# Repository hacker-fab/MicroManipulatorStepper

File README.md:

# HackerFab Nanopositioner

This repository contains **HackerFab’s extended version** of the open-source nanopositioner originally developed by Diffraction Limited.

We build directly on the original design and contribute additional capabilities, including:
- Rotational control
- Integrated heating
- Vacuum compatibility
- Ongoing improvements for lab use at HackerFab

## Credit

All core mechanical, electrical, and firmware design work is credited to the original project:

https://github.com/0x23/OpenMicroManipulator  

This repo is a derivative work that extends their platform for new use cases with additional custom made components. 

## Documentation

For build instructions, usage, and full system details, see the HackerFab documentation:

https://docs.hackerfab.org/home

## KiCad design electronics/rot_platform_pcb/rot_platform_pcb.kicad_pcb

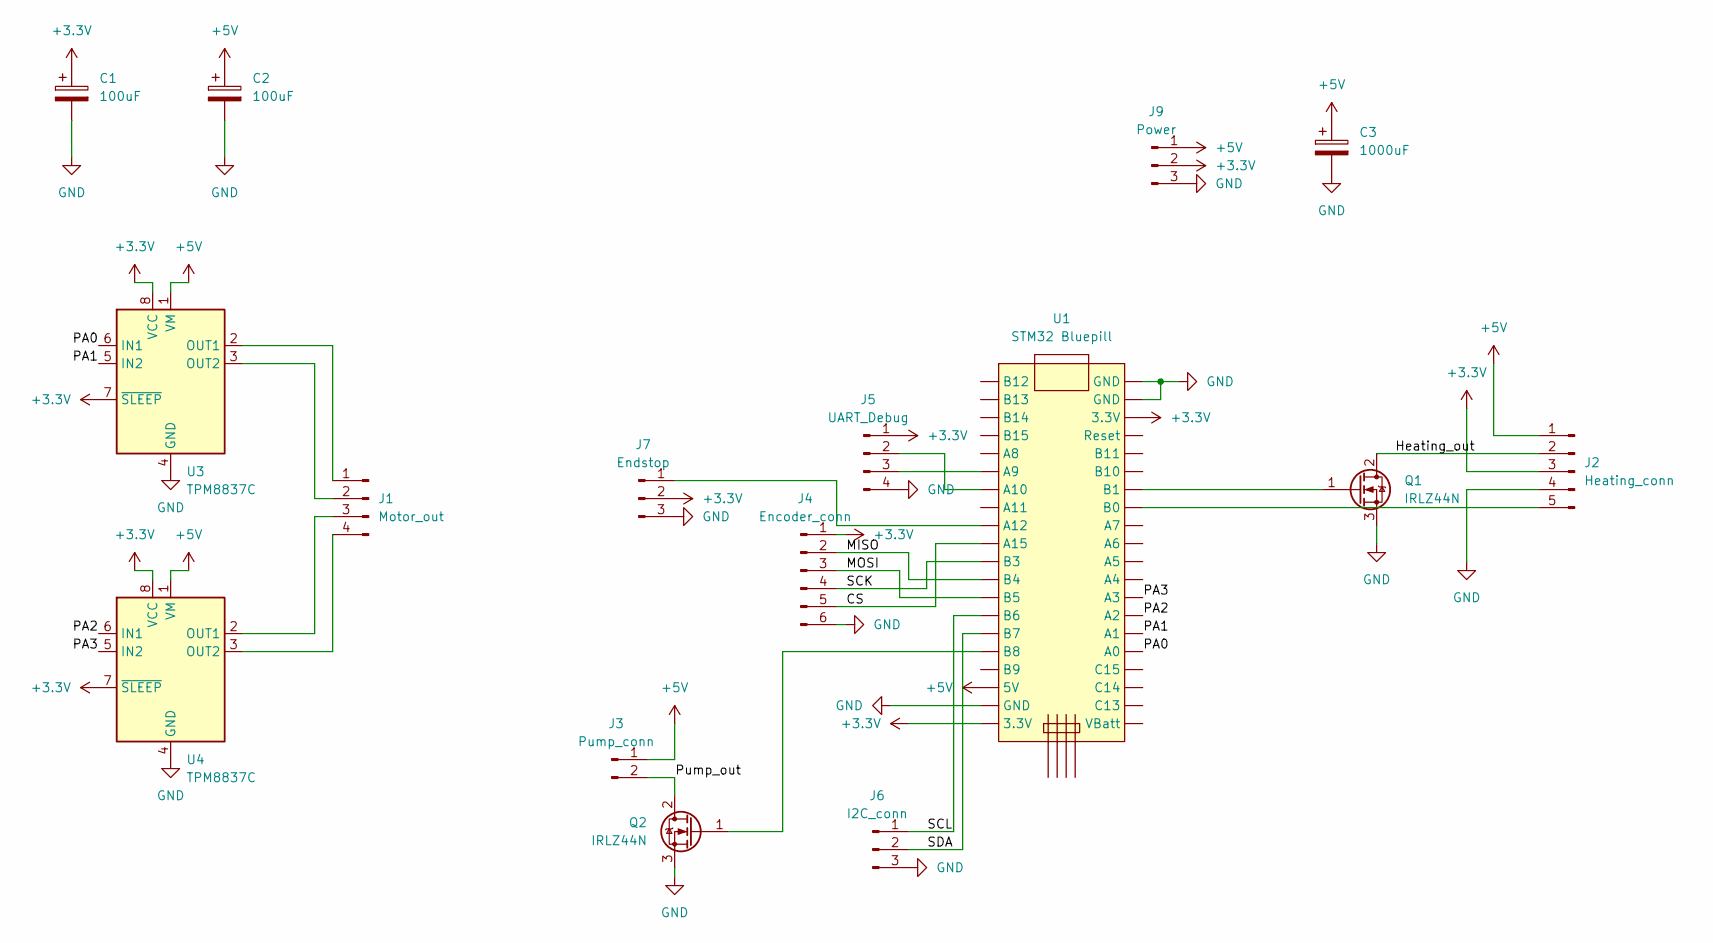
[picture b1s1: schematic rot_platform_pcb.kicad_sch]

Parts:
C1, C2: 100uF; CP_Radial_D5.0mm_P2.50mm
C3: 1000uF; CP_Radial_D10.0mm_P5.00mm
J1: Motor_out; PinHeader_1x04_P2.54mm_Vertical
J2: Heating_conn; PinHeader_1x05_P2.54mm_Vertical
J3: Pump_conn; PinHeader_1x02_P2.54mm_Vertical
J4: Encoder_conn; PinHeader_1x06_P2.54mm_Vertical
J5: UART_Debug; PinHeader_1x04_P2.54mm_Vertical
J6: I2C_conn; PinHeader_1x03_P2.54mm_Vertical
J7: Endstop; PinHeader_1x03_P2.54mm_Vertical
J9: Power; PinHeader_1x03_P2.54mm_Vertical
Q1, Q2: IRLZ44N; TO-220-3_Vertical
U1: STM32 Bluepill; stm32_bluepill
U3, U4: TPM8837C; SOIC-8-1EP_3.9x4.9mm_P1.27mm_EP2.29x3mm

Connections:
+3.3V: C1.1, J2.3, J4.1, J5.1, J7.2, J9.2, U1.20 (3.3V), U1.38 (3.3V), U3.7 (~SLEEP), U3.8 (VCC), U4.7 (~SLEEP), U4.8 (VCC)
+5V: C2.1, C3.1, J2.1, J3.1, J9.1, U1.18 (5V), U3.1 (VM), U4.1 (VM)
/CS: J4.5, U1.10 (A15)
/Heating_out: J2.2, Q1.2 (D)
/MISO: J4.2, U1.12 (B4)
/MOSI: J4.3, U1.13 (B5)
/PA0: U1.25 (A0), U3.6 (IN1)
/PA1: U1.26 (A1), U3.5 (IN2)
/PA2: U1.27 (A2), U4.6 (IN1)
/PA3: U1.28 (A3), U4.5 (IN2)
/Pump_out: J3.2, Q2.2 (D)
/SCK: J4.4, U1.11 (B3)
/SCL: J6.1, U1.14 (B6)
/SDA: J6.2, U1.15 (B7)
/Temp_in: J2.5, U1.33 (B0); also elsewhere on the board
GND: C1.2, C2.2, C3.2, J2.4, J4.6, J5.4, J6.3, J7.3, J9.3, Q1.3 (S), Q2.3 (S), U1.19 (GND), U1.39 (GND), U1.40 (GND), U3.4 (GND), U3.9 (GND), U4.4 (GND), U4.9 (GND); also elsewhere on the board
unnamed: J1.1, U3.2 (OUT1)
unnamed: J1.2, U3.3 (OUT2)
unnamed: J1.3, U4.2 (OUT1)
unnamed: J1.4, U4.3 (OUT2)
unnamed: J5.2, U1.7 (A10)
unnamed: J5.3, U1.6 (A9)
unnamed: J7.1, U1.9 (A12)
unnamed: Q1.1 (G), U1.34 (B1)
unnamed: Q2.1 (G), U1.16 (B8)

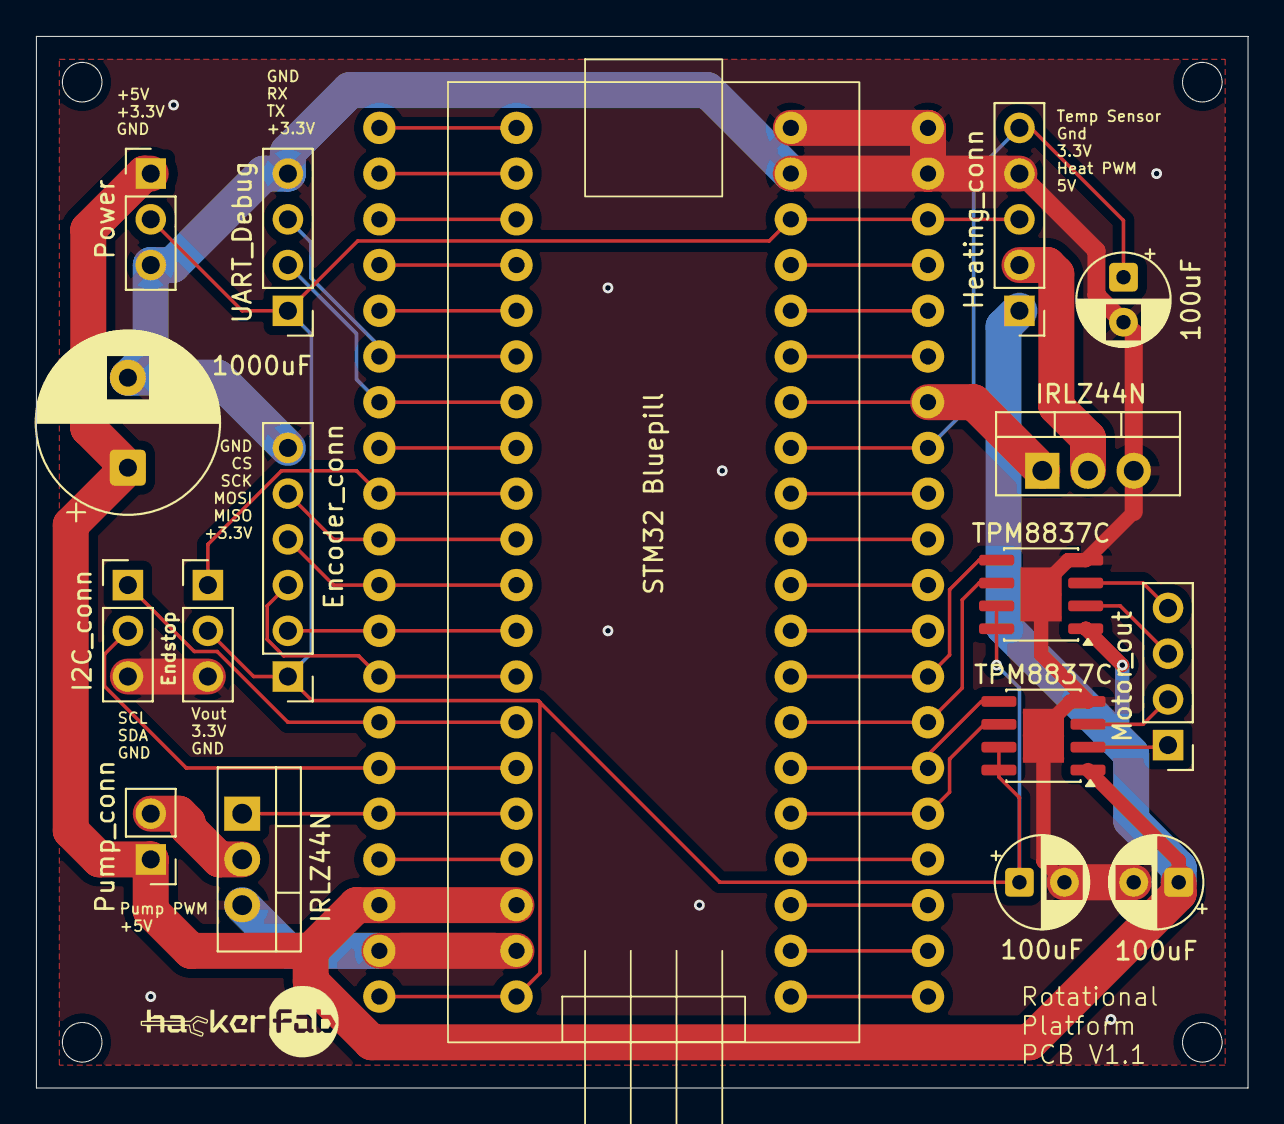
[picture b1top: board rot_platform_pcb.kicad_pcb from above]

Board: 2 copper layers, 67.3 x 58.4 mm, 17 parts (0 on the bottom side), 25 nets.

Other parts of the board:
C4: 100uF; CP_Radial_D5.0mm_P2.50mm

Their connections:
/Temp_in: C4.1; also elsewhere on the board
GND: C4.2; also elsewhere on the board

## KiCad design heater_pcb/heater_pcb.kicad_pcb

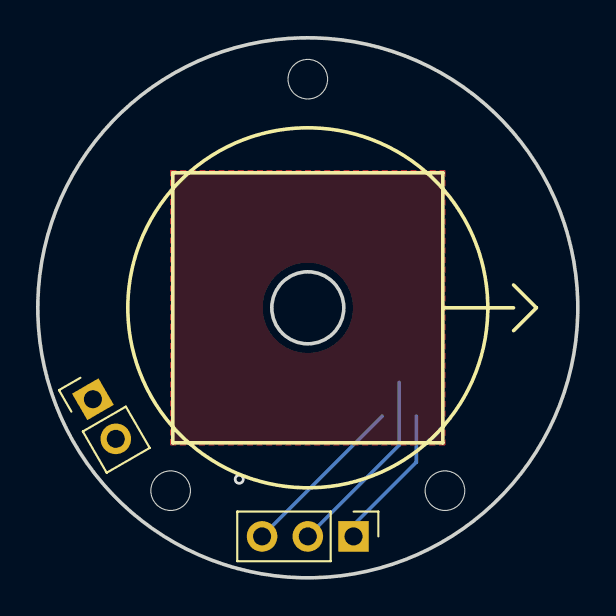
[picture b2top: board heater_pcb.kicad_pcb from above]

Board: 4 copper layers, 30.0 x 30.0 mm, 3 parts (1 on the bottom side), 4 nets.

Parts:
J2: Conn_01x02_Pin; PinHeader_1x02_P2.54mm_Vertical
J3: Conn_01x03_Pin; PinHeader_1x03_P2.54mm_Vertical
U1: MCP9700Ax-ETT; SOT-23

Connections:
/GND: J3.2, U1.3 (GND)
/VDD: J3.1, U1.1 (V_{DD})
/Vout: J3.3, U1.2 (V_{OUT})
/heat_trace: J2.1, J2.2

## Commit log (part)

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2026-02-19 add rotation controller code
2026-02-26 implement rotation homing
2026-03-08 add heating pin defs
2026-03-11 Updates and things
2026-03-12 add vacuum
2026-03-12 move temperature to separate file
2026-03-12 move rotation to separate file
2026-03-16 Update with more v4 tests
2026-03-16 fix i2c issues
2026-03-18 Updates and stuff
2026-03-20 Updates for working!!!
2026-03-23 Fix homing retraction angle
2026-03-27 Move Image Validation to its own piece of software
2026-03-30 Update for custom delay
2026-03-30 Update with better homing for z axis
2026-03-31 Update with intro info
2026-04-03 add PCB design files
2026-04-03 Update with better public functions
2026-04-03 implement proper value reads
2026-04-03 update lookup table, add rotation speed limit
2026-04-06 Updates with initial peripheral code
2026-04-06 Update with peripheral GCode commands
2026-04-07 Test perms
2026-04-08 Updates to stage usage
2026-04-08 Revert peripheral changes
2026-04-08 Working Version
2026-04-10 integration tested version
2026-04-15 CMake + Tests
2026-04-15 Docs
2026-04-15 Revert "Implement CMake + Unit Tests (#2)"
    This reverts commit e1f5db52afb366a841be8723e401f3fc3166c684.
2026-04-15 Revert "Implement CMake + Unit Tests (#2)" (#3)
    This reverts commit e1f5db52afb366a841be8723e401f3fc3166c684.
2026-04-20 fix rotation negative sign issue, add warning message for encoder
2026-04-21 update rotational stage PCB to V1.1
    Fixed a few issues in V1.0
2026-04-21 cleaned up unused rotation code
2026-04-21 Update vibration detector for more
2026-04-29 clean up code and fixes on PCB (#4)
    * fix rotation negative sign issue, add warning message for encoder
    * update rotational stage PCB to V1.1
    Fixed a few issues in V1.0
    * add home and calibration debug command
    * cleaned up unused rotation code
2026-04-29 Updates with Step
2026-05-03 Add holder stl
2026-05-03 Rename Assembly_MicroManipulator-Assembly_MicroManipulator - Part 174.stl to StandingBase.stl
